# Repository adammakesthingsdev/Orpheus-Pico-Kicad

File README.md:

# Orpheus Pico
## About this repo
Welcome to the Kicad port of the Orpheus Pico, Hack Club's very own Raspberry Pi Pico compatible microcontroller!
This repository contains both the project files and built gerbers for ordering through JLCPCB.
Please note, **ordering is at your own risk**: I will not be held accountable if you have problems due to mistakes made ordering or issues with the project.

## Ordering
For information on ordering these boards, please refer to ORDERING.md.

## Licensing / other info
An official license for this project is TBD.
For now, you can:
- Use this project for inspiration and derivatives
- Order Orpheus Picos for **non-commercial** purposes: This means you cannot sell them, even at cost

Please get in touch with me (@adammakesthings on Hack Club Slack or adam@hackclub.com) if you are planning on selling Orpheus Picos or ordering large quantities.  

My final ask is that if you order any Orpheus Picos for any reason, I ask that you please keep my name and attribution on them. Again, please get in touch if this doesn't work for you.  
  
-Adam G

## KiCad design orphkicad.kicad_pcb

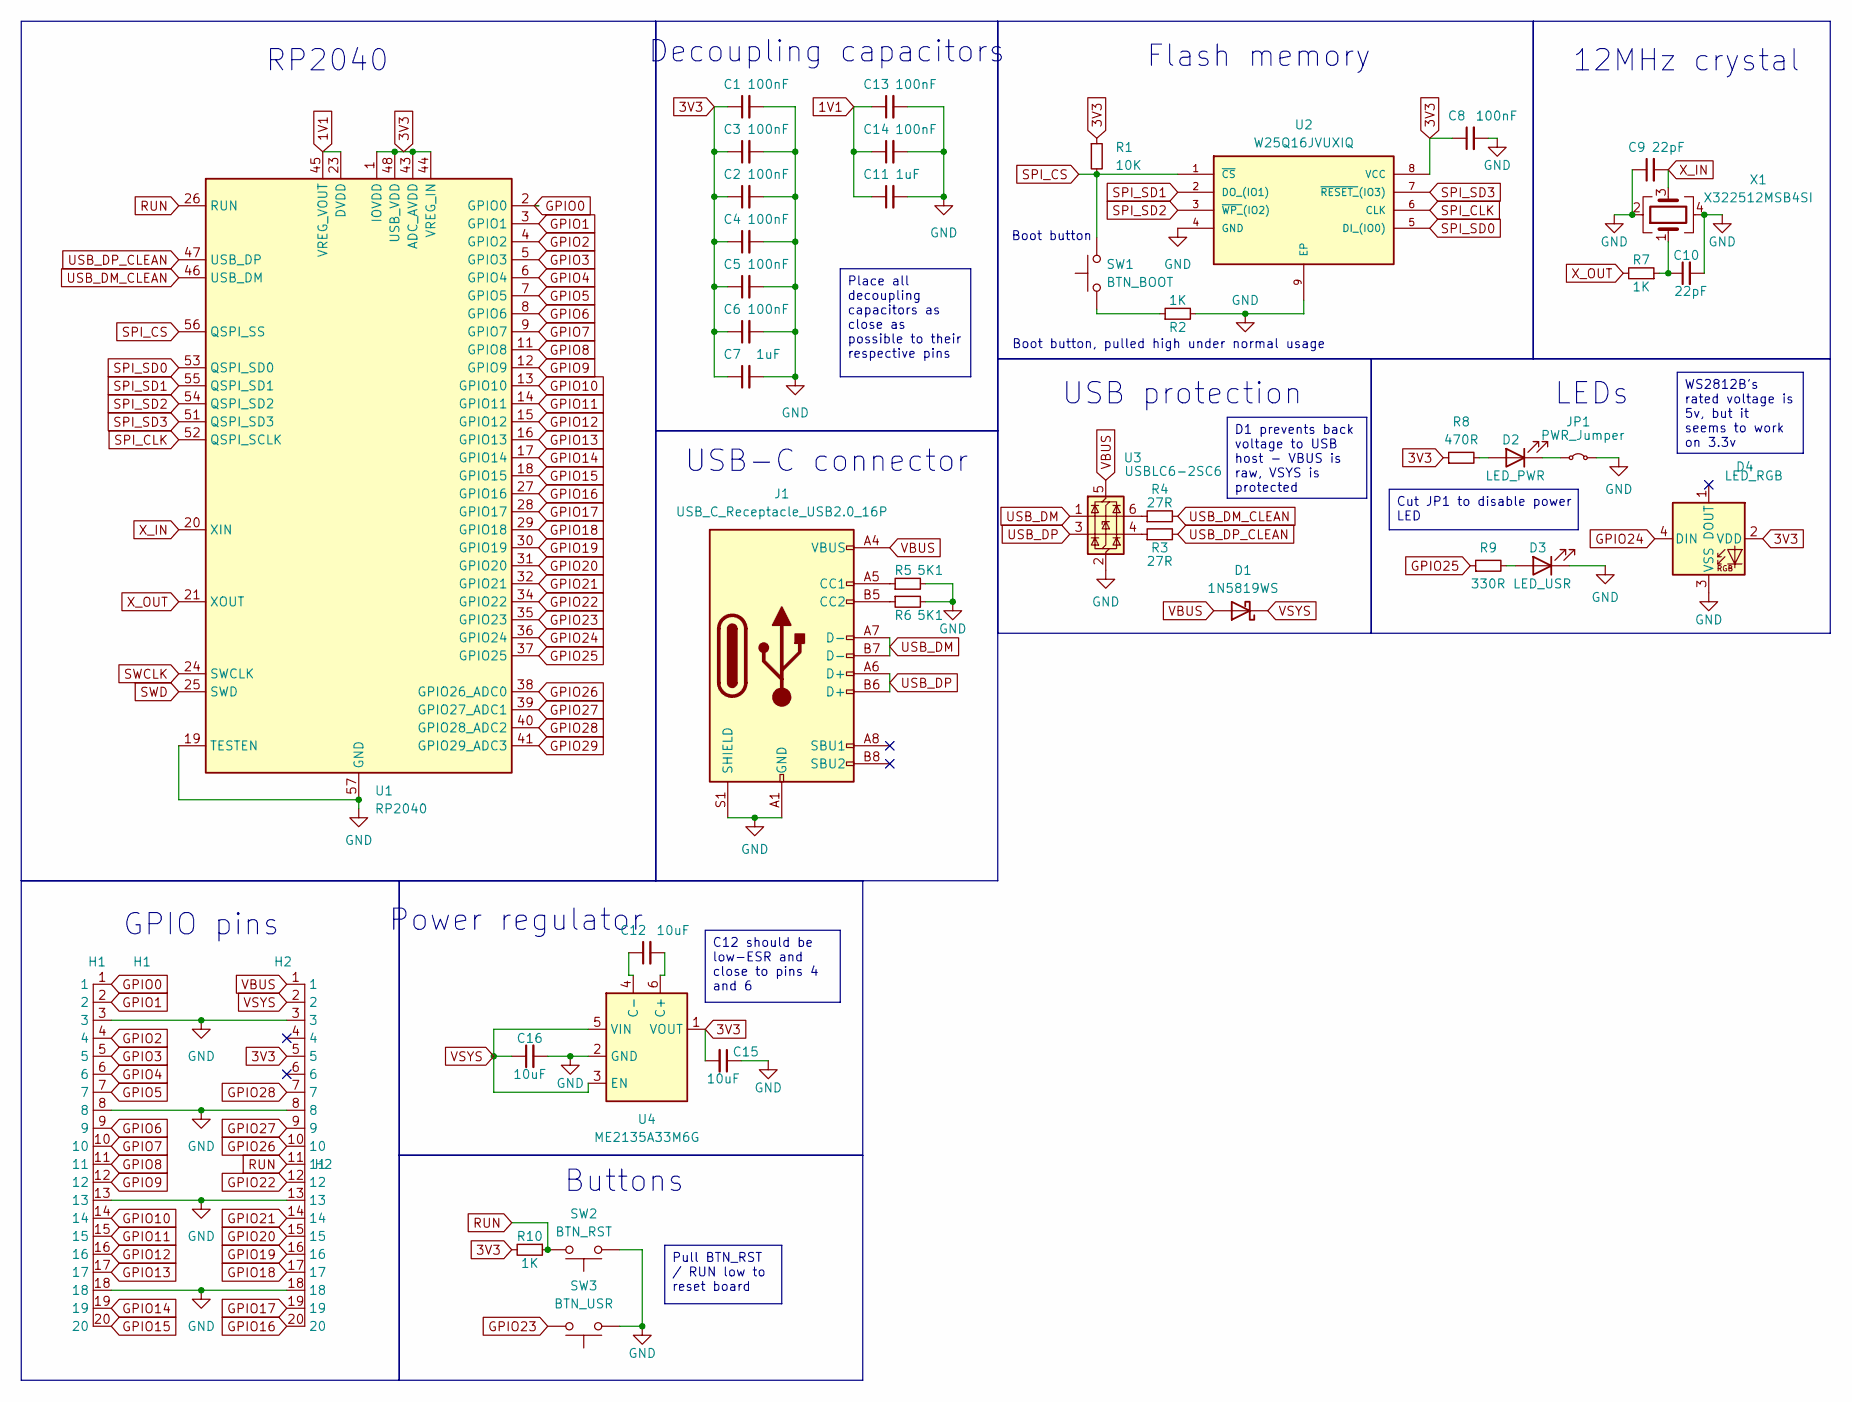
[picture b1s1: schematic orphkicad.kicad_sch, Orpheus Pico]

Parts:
C1, C2, C3, C4, C5, C6, C8, C13, C14: 100nF; C_0402_1005Metric
C7, C11: 1uF; C_0402_1005Metric
C9, C10: 22pF; C_0402_1005Metric
C12: 10uF; C_0805_2012Metric
C15, C16: 10uF; C_0402_1005Metric
D1: 1N5819WS; D_SOD-323
D2: LED_PWR; LED_0603_1608Metric
D3: LED_USR; LED_0603_1608Metric
D4: LED_RGB; LED-SMD_4P-L1.6-W1.5_XL-1615RGBC-WS2812B
H1: H1; OrphPicoHeaders
H2: H2; OrphPicoHeaders
J1: USB_C_Receptacle_USB2.0_16P; USB-C-SMD_TYPE-C-6PIN-2MD-073
JP1: PWR_Jumper; SolderJumper-2_P1.3mm_Bridged2Bar_RoundedPad1.0x1.5mm
R1: 10K; R_0402_1005Metric
R2, R7, R10: 1K; R_0402_1005Metric
R3, R4: 27R; R_0402_1005Metric
R5, R6: 5K1; R_0402_1005Metric
R8: 470R; R_0402_1005Metric
R9: 330R; R_0402_1005Metric
SW1: BTN_BOOT; SW-SMD_L3.9-W3.0-P4.45
SW2: BTN_RST; SW-SMD_L3.9-W3.0-P4.45
SW3: BTN_USR; SW-SMD_L3.9-W3.0-P4.45
U1: RP2040; QFN-56-1EP_7x7mm_P0.4mm_EP3.2x3.2mm
U2: W25Q16JVUXIQ; Winbond_USON-8-1EP_3x2mm_P0.5mm_EP0.2x1.6mm; MANUFACTURER_PART_NUMBER W25Q16JVUXIQ; LCSC C2843335
U3: USBLC6-2SC6; SOT-23-6
U4: ME2135A33M6G; SOT-23-6; LCSC C610271
X1: X322512MSB4SI; Crystal_SMD_3225-4Pin_3.2x2.5mm; LCSC C9002

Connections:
1V1: C11.1, C13.1, C14.1, U1.23 (DVDD), U1.45 (VREG_VOUT), U1.50 (DVDD)
3V3: C1.1, C2.1, C3.1, C4.1, C5.1, C6.1, C7.1, C8.1, C15.2, D4.2 (VDD), H2.5, R1.1, R8.1, R10.2, U1.1 (IOVDD), U1.10 (IOVDD), U1.22 (IOVDD), U1.33 (IOVDD), U1.42 (IOVDD), U1.43 (ADC_AVDD), U1.44 (VREG_IN), U1.48 (USB_VDD), U1.49 (IOVDD), U2.8 (VCC), U4.1 (VOUT)
GND: C1.2, C2.2, C3.2, C4.2, C5.2, C6.2, C7.2, C8.2, C9.1, C10.2, C11.2, C13.2, C14.2, C15.1, C16.2, D3.1 (K), D4.3 (VSS), H1.3, H1.8, H1.13, H1.18, H2.3, H2.8, H2.13, H2.18, J1.A1 (GND), J1.B1 (GND), J1.S1 (SHIELD), JP1.2 (B), R2.2, R5.2, R6.2, SW2.1, SW3.1, U1.19 (TESTEN), U1.57 (GND), U2.4 (GND), U2.9 (EP), U3.2 (GND), U4.2 (GND), X1.2, X1.4
GPIO0: H1.1, U1.2 (GPIO0)
GPIO1: H1.2, U1.3 (GPIO1)
GPIO2: H1.4, U1.4 (GPIO2)
GPIO3: H1.5, U1.5 (GPIO3)
GPIO4: H1.6, U1.6 (GPIO4)
GPIO5: H1.7, U1.7 (GPIO5)
GPIO6: H1.9, U1.8 (GPIO6)
GPIO7: H1.10, U1.9 (GPIO7)
GPIO8: H1.11, U1.11 (GPIO8)
GPIO9: H1.12, U1.12 (GPIO9)
GPIO10: H1.14, U1.13 (GPIO10)
GPIO11: H1.15, U1.14 (GPIO11)
GPIO12: H1.16, U1.15 (GPIO12)
GPIO13: H1.17, U1.16 (GPIO13)
GPIO14: H1.19, U1.17 (GPIO14)
GPIO15: H1.20, U1.18 (GPIO15)
GPIO16: H2.20, U1.27 (GPIO16)
GPIO17: H2.19, U1.28 (GPIO17)
GPIO18: H2.17, U1.29 (GPIO18)
GPIO19: H2.16, U1.30 (GPIO19)
GPIO20: H2.15, U1.31 (GPIO20)
GPIO21: H2.14, U1.32 (GPIO21)
GPIO22: H2.12, U1.34 (GPIO22)
GPIO23: SW3.2, U1.35 (GPIO23)
GPIO24: D4.4 (DIN), U1.36 (GPIO24)
GPIO25: R9.1, U1.37 (GPIO25)
GPIO26: H2.10, U1.38 (GPIO26_ADC0)
GPIO27: H2.9, U1.39 (GPIO27_ADC1)
GPIO28: H2.7, U1.40 (GPIO28_ADC2)
GPIO29: U1.41 (GPIO29_ADC3)
unnamed: C10.1, R7.1, X1.1
unnamed: D2.2 (A), R8.2
unnamed: D2.1 (K), JP1.1 (A)
unnamed: D3.2 (A), R9.2
unnamed: J1.A5 (CC1), R5.1
unnamed: J1.B5 (CC2), R6.1
unnamed: R2.1, SW1.1
unnamed: R3.1, U3.4 (I/O2)
unnamed: R4.1, U3.6 (I/O1)
unnamed: C12.2, U4.6 (C+)
unnamed: C12.1, U4.4 (C-)
RUN: H2.11, R10.1, SW2.2, U1.26 (RUN)
SPI_CLK: U1.52 (QSPI_SCLK), U2.6 (CLK)
SPI_CS: R1.2, SW1.2, U1.56 (QSPI_SS), U2.1 (~CS)
SPI_SD0: U1.53 (QSPI_SD0), U2.5 (DI_(IO0))
SPI_SD1: U1.55 (QSPI_SD1), U2.2 (DO_(IO1))
SPI_SD2: U1.54 (QSPI_SD2), U2.3 (~WP_(IO2))
SPI_SD3: U1.51 (QSPI_SD3), U2.7 (~RESET_(IO3))
SWCLK: U1.24 (SWCLK)
SWD: U1.25 (SWD)
USB_DM: J1.A7 (D-), J1.B7 (D-), U3.1 (I/O1)
USB_DM_CLEAN: R4.2, U1.46 (USB_DM)
USB_DP: J1.A6 (D+), J1.B6 (D+), U3.3 (I/O2)
USB_DP_CLEAN: R3.2, U1.47 (USB_DP)
VBUS: D1.2 (A), H2.1, J1.A4 (VBUS), J1.B4 (VBUS), U3.5 (VBUS)
VSYS: C16.1, D1.1 (K), H2.2, U4.3 (EN), U4.5 (VIN)
X_IN: C9.2, U1.20 (XIN), X1.3
X_OUT: R7.2, U1.21 (XOUT)

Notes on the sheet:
Power regulator
Flash memory
Boot button, pulled high under normal usage
USB-C connector
Decoupling capacitors
USB protection
LEDs
Boot button
RP2040
GPIO pins
Buttons
12MHz crystal
Pull BTN_RST / RUN low to reset board
Place all decoupling capacitors as close as possible to their respective pins
WS2812B's rated voltage is 5v, but it seems to work on 3.3v
C12 should be low-ESR and close to pins 4 and 6
Cut JP1 to disable power LED
D1 prevents back voltage to USB host - VBUS is raw, VSYS is protected

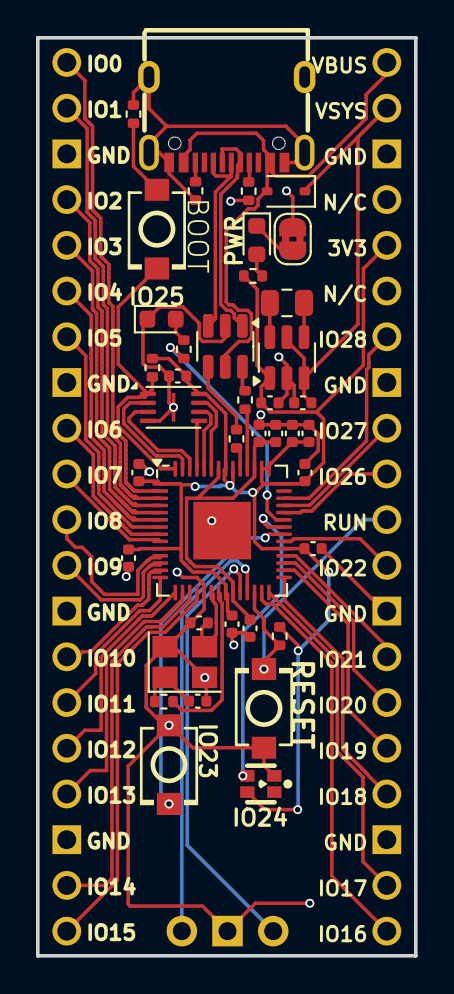
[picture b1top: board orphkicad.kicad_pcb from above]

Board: 2 copper layers, 21.0 x 51.0 mm, 42 parts (0 on the bottom side), 58 nets.

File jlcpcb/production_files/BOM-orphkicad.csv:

Comment,Designator,Footprint,LCSC,Quantity
1K,"R10,R2,R7",R_0402_1005Metric,C11702,3
100nF,"C1,C13,C14,C2,C3,C4,C5,C6,C8",C_0402_1005Metric,C1525,9
10uF,"C15,C16",C_0402_1005Metric,C15525,2
22pF,"C10,C9",C_0402_1005Metric,C1555,2
10uF,C12,C_0805_2012Metric,C15850,1
1N5819WS,D1,D_SOD-323,C191023,1
RP2040,U1,QFN-56-1EP_7x7mm_P0.4mm_EP3.2x3.2mm,C2040,1
LED_PWR,D2,LED_0603_1608Metric,C2286,1
27R,"R3,R4",R_0402_1005Metric,C25100,2
330R,R9,R_0402_1005Metric,C25104,1
470R,R8,R_0402_1005Metric,C25117,1
10K,R1,R_0402_1005Metric,C25744,1
5K1,"R5,R6",R_0402_1005Metric,C25905,2
USB_C_Receptacle_USB2.0_16P,J1,USB-C-SMD_TYPE-C-6PIN-2MD-073,C2765186,1
W25Q16JVUXIQ,U2,Winbond_USON-8-1EP_3x2mm_P0.5mm_EP0.2x1.6mm,C2843335,1
BTN_BOOT,"SW1,SW2,SW3",SW-SMD_L3.9-W3.0-P4.45,C455280,3
USBLC6-2SC6,U3,SOT-23-6,C5180249,1
1uF,"C11,C7",C_0402_1005Metric,C52923,2
LED_RGB,D4,LED-SMD_4P-L1.6-W1.5_XL-1615RGBC-WS2812B,C5349954,1
ME2135A33M6G,U4,SOT-23-6,C610271,1
X322512MSB4SI,X1,Crystal_SMD_3225-4Pin_3.2x2.5mm,C9002,1
LED_USR,D3,LED_0603_1608Metric,C965804,1

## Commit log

2025-07-21 Initial commit - adds JLCPCB production files and KiCad project files
2025-07-21 Dejankifies back plane routing
    Routing on the back plane is now a little less janky, at the cost of a more segmented back plane.
2025-07-21 Adds ordering info document
2025-07-22 Adds README
